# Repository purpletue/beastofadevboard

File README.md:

# BEEFCAKE 
*The absolute unit of a dual-MCU, hardwired, matrix-slinging, analog-crunching dev board.*

## What is BEEFCAKE?
BEEFCAKE isn't just a microcontroller board; it's a statement. Built out of sheer spite for unreliable wireless dropouts and a desire to completely over-engineer a hardware project, BEEFCAKE combines dual RP2040 microcontrollers, rock-solid hardwired Ethernet, an 8x8 LED matrix driven by a dedicated controller, an NFC reader/writer, and an ungodly number of GPIOs into a single top-mounted layout masterpiece.

## Key Features
* **Dual RP2040 Architecture:** 
  * **The Master ("Pimp"):** Handles heavy networking, system logic, and boasts 30 usable GPIOs.
  * **The Peripheral Slave ("Whore"):** Dedicated purely to analog-crunching, keeping its full suite of ADC channels completely pristine and isolated from digital noise.
* **Hardwired Ethernet:** Powered by a W5500 Ethernet stack and an RJ45 port because Wi-Fi is weak and cables are forever.
* **Matrix Vision:** Features an 8x8 LED matrix driven by a MAX7219 IC, paired with a custom NeoPixel button for maximum tactile satisfaction.
* **NFC Integration:** Built-in STMicroelectronics NFC reader/writer capabilities (ST25R3911B) for contactless sorcery.
* **Expansion Galore:** 
  * A 6-pin JST expansion connector wired straight to a clean SPI bus (3.3V, GND, SCK, MOSI, MISO, CS) to leave zero digital pins wasted.
  * A USB-C receptacle for power and programming.
* **Tactile Input:** On-board tactile buttons and test points for debugging sanity.

## Pinout & Hardware Specs
* **Total Master GPIO:** 30 available pins.
* **Total System ADCs:** 8 channels across the board (isolated cleanly on the slave).
* **Display Driver:** MAX7219 (SOIC-24 Wide) driving the 8x8 LED grid.
* **Network:** W5500 SPI Ethernet Controller + RJ45 with integrated magnetics.

---

### Serious now: AI Usage declaration.
This project uses AI in the README.md and nowhere else.

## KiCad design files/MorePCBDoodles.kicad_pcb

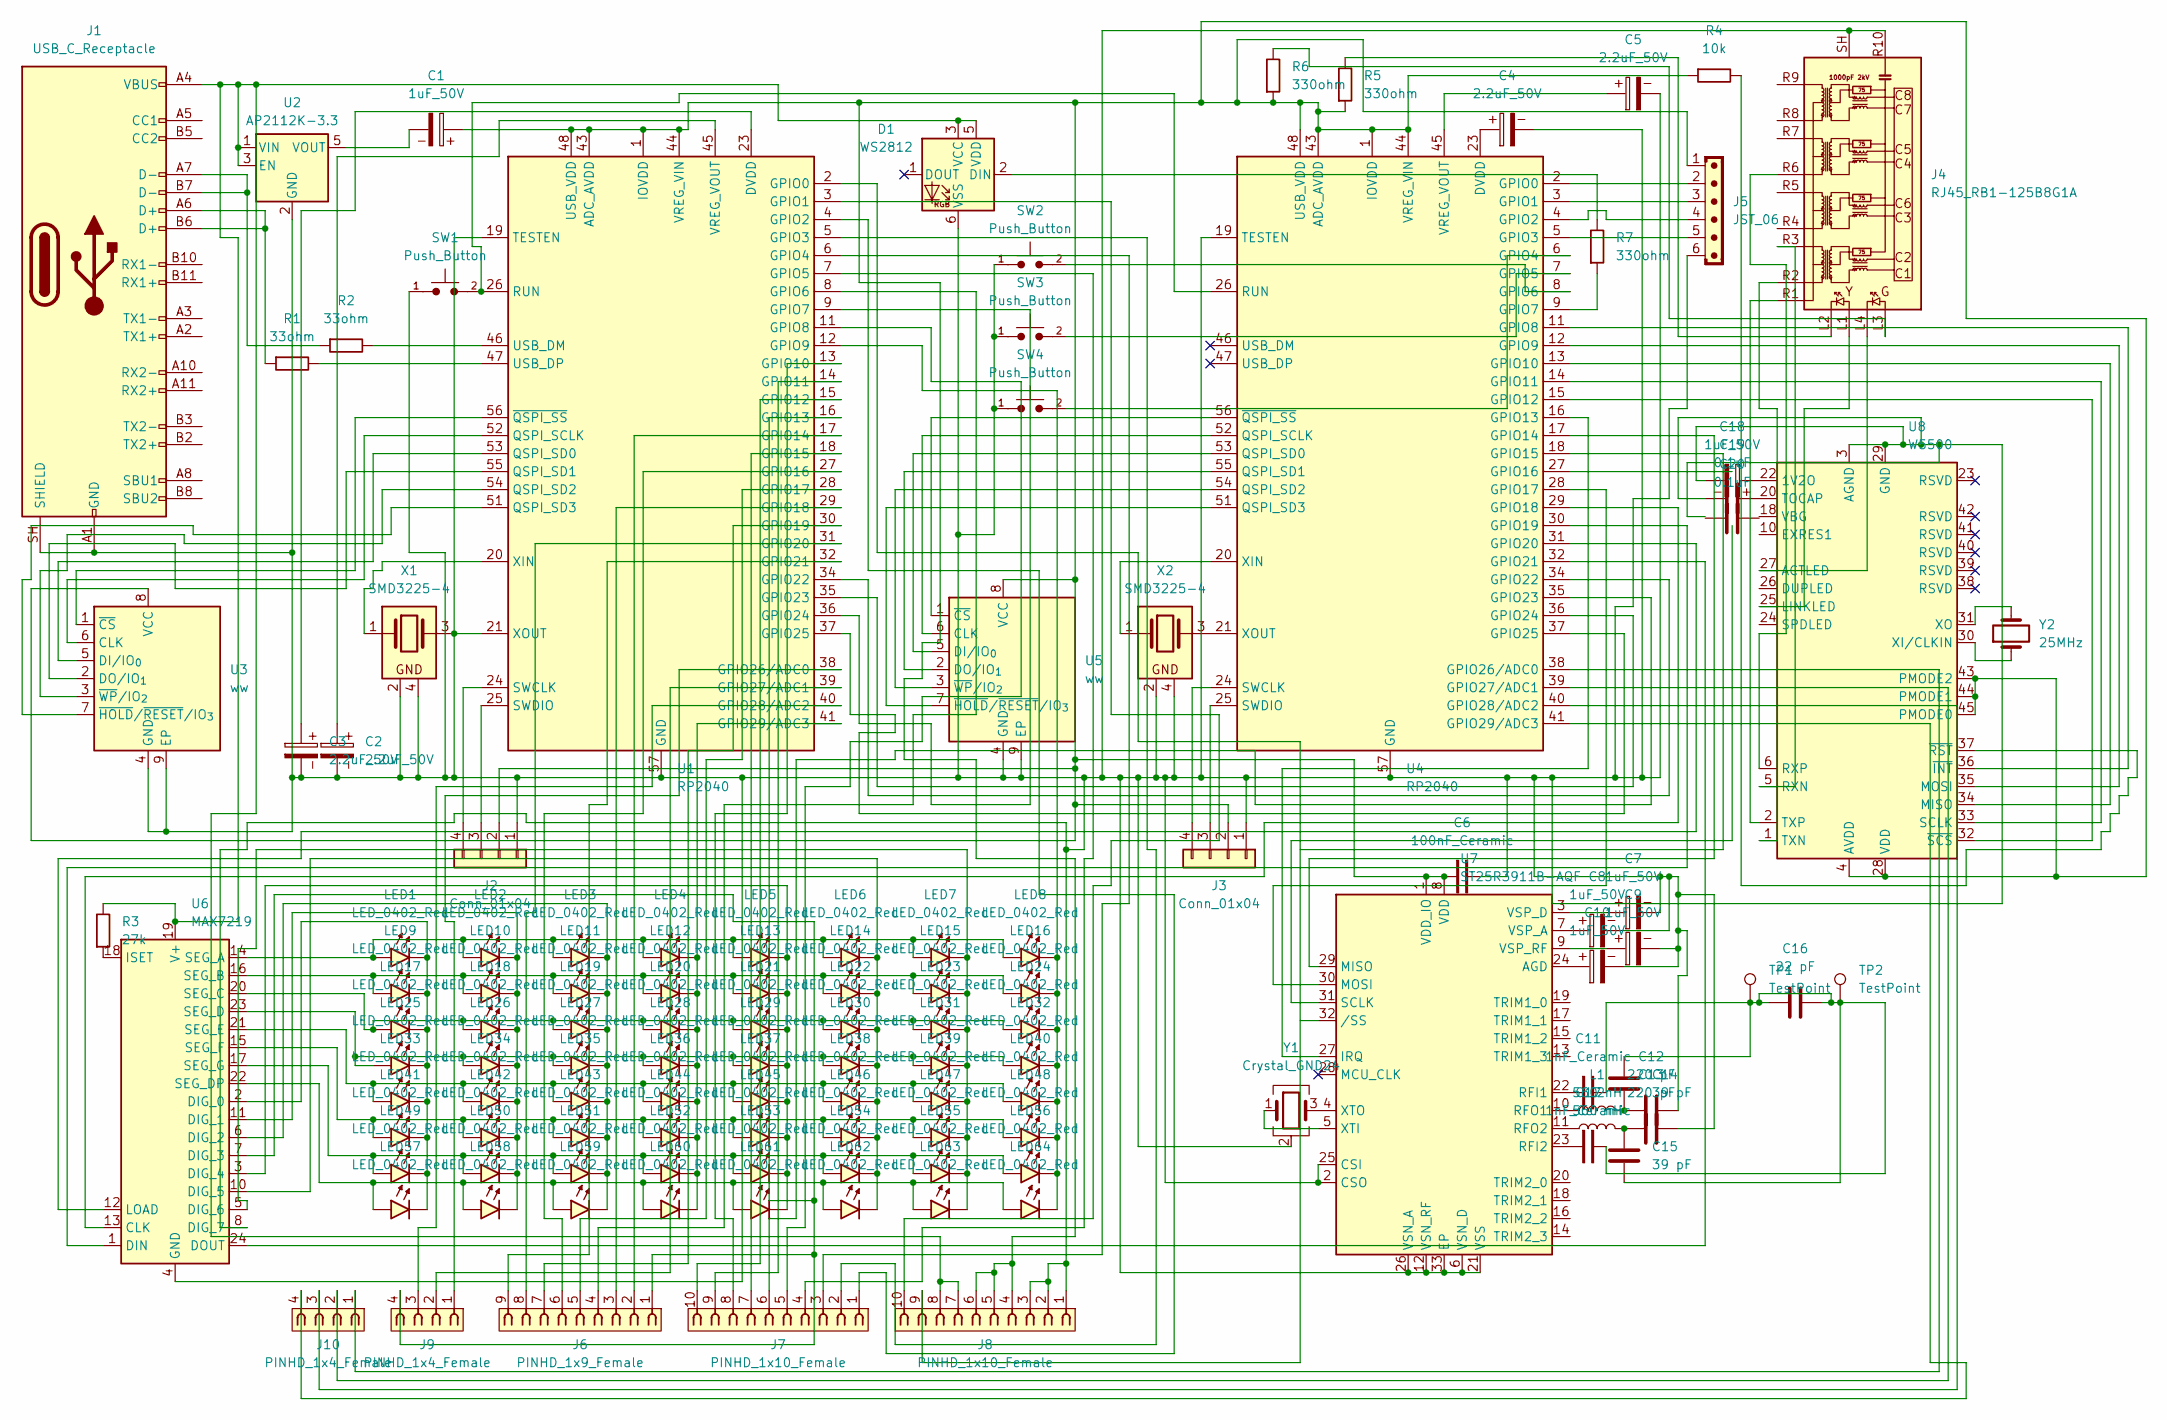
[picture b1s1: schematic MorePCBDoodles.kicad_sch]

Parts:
C1, C7, C8, C9, C10, C18: 1uF_50V; CP_Radial_D4.0mm_P1.50mm
C2, C3, C4, C5: 2.2uF_50V; CP_Radial_D4.0mm_P1.50mm
C6: 100nF_Ceramic; C_Disc_D5.0mm_W2.5mm_P2.50mm
C11, C17: 1nF_Ceramic; C_Disc_D5.0mm_W2.5mm_P2.50mm
C12, C13: 220 pF; CP_Axial_L10.0mm_D4.5mm_P15.00mm_Horizontal
C14, C15: 39 pF; CP_Axial_L10.0mm_D4.5mm_P15.00mm_Horizontal
C16: 22 pF; CP_Axial_L10.0mm_D4.5mm_P15.00mm_Horizontal
C19, C20: 0.1uF; CP_Elec_3x5.3
D1: WS2812; LED_WS2812_PLCC6_5.0x5.0mm_P1.6mm
J1: USB_C_Receptacle; USB_C_Receptacle_Amphenol_124019772112A
J2, J3: Conn_01x04; PinHeader_1x04_P1.00mm_Horizontal
J4: RJ45_RB1-125B8G1A; RJ45_UDE_RB1-125B8G1A
J5: JST_06; JST_EH_B6B-EH-A_1x06_P2.50mm_Vertical
J6: PINHD_1x9_Female; PinSocket_1x09_P2.54mm_Vertical
J7, J8: PINHD_1x10_Female; PinSocket_1x10_P2.54mm_Vertical
J9, J10: PINHD_1x4_Female; PinSocket_1x04_P2.54mm_Vertical
L1, L2: 560 nH; L_01005_0402Metric
LED1, LED2, LED3, LED4, LED5, LED6, LED7, LED8, LED9, LED10, LED11, LED12, LED13, LED14, LED15, LED16, LED17, LED18, LED19, LED20, LED21, LED22, LED23, LED24, LED25, LED26, LED27, LED28, LED29, LED30, LED31, LED32, LED33, LED34, LED35, LED36, LED37, LED38, LED39, LED40, LED41, LED42, LED43, LED44, LED45, LED46, LED47, LED48, LED49, LED50, LED51, LED52, LED53, LED54, LED55, LED56, LED57, LED58, LED59, LED60, LED61, LED62, LED63, LED64: LED_0402_Red; LED_0402_1005Metric
R1, R2: 33ohm; R_Axial_DIN0207_L6.3mm_D2.5mm_P10.16mm_Horizontal
R3: 27k; R_Axial_DIN0207_L6.3mm_D2.5mm_P10.16mm_Horizontal
R4: 10k; R_Axial_DIN0207_L6.3mm_D2.5mm_P10.16mm_Horizontal
R5, R6, R7: 330ohm; R_Axial_DIN0207_L6.3mm_D2.5mm_P10.16mm_Horizontal
SW1, SW2, SW3, SW4: Push_Button; SW_SPST_TS-1088-xR020
TP1, TP2: TestPoint; TestPoint_Pad_1.0x1.0mm
U1, U4: RP2040; QFN-56-1EP_7x7mm_P0.4mm_EP3.2x3.2mm
U2: AP2112K-3.3; SOT-23-5
U3, U5: ww; WSON-8-1EP_8x6mm_P1.27mm_EP3.4x4.3mm
U6: MAX7219; SOIC-24W_7.5x15.4mm_P1.27mm
U7: ST25R3911B-AQF; QFN-32-1EP_5x5mm_P0.5mm_EP3.6x3.6mm_ThermalVias
U8: W5500; LQFP-48_7x7mm_P0.5mm
X1, X2: SMD3225-4; Crystal_SMD_3225-4Pin_3.2x2.5mm
Y1: Crystal_GND24; Crystal_SMD_3225-4Pin_3.2x2.5mm
Y2: 25MHz; Crystal_SMD_3225-4Pin_3.2x2.5mm

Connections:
unnamed: C3.1, U1.23 (DVDD), U1.50 (DVDD)
unnamed: C4.1, U4.23 (DVDD), U4.50 (DVDD)
unnamed: C11.2, C14.2, C15.1, C16.1, C16.2, C17.2, TP1.1 (1_1), TP2.1 (1_1)
unnamed: C12.1, C14.1, L1.2
unnamed: C13.1, C15.2, L2.2
unnamed: D1.2 (DIN), R7.2
unnamed: D1.3 (VCC), D1.5 (VDD), J1.A4 (VBUS), J1.A9 (VBUS), J1.B4 (VBUS), J1.B9 (VBUS), J8.7, J8.8, R3.2, U2.1 (VIN), U2.3 (EN), U6.19 (V+)
unnamed: C2.2, C3.2, C4.2, C5.2, C6.2, C7.2, C8.2, C9.2, C10.2, C12.2, C13.2, C18.2, C19.2, D1.6 (VSS), J1.A1 (GND), J1.A12 (GND), J1.B1 (GND), J1.B12 (GND), J1.SH (SHIELD), J2.1, J3.1, J4.R10 (GND), J4.SH, J5.6, J8.1, J8.2, J8.3, SW1.1, SW2.1, SW3.1, SW4.1, U1.19 (TESTEN), U1.21 (XOUT), U1.57 (GND), U2.2 (GND), U3.4 (GND), U3.9 (EP), U4.19 (TESTEN), U4.57 (GND), U5.4 (GND), U5.9 (EP), U6.4 (GND), U6.8 (DIG_7), U6.9 (GND), U7.2 (CSO), U7.6 (VSN_D), U7.12 (VSN_RF), U7.21 (VSS), U7.25 (CSI), U7.26 (VSN_A), U7.33 (EP), U8.3 (AGND), U8.9 (AGND), U8.14 (AGND), U8.16 (AGND), U8.19 (AGND), U8.29 (GND), U8.48 (AGND), X1.2, X1.3, X1.4, X2.2, X2.4, Y1.2 (G), Y1.4 (G)
unnamed: J1.A6 (D+), J1.B6 (D+), R1.1
unnamed: J1.A7 (D-), J1.B7 (D-), R2.1
unnamed: C1.1, C6.1, J2.2, J3.2, J5.1, J8.4, J8.5, J8.6, R4.1, R5.1, R6.1, U1.1 (IOVDD), U1.10 (IOVDD), U1.22 (IOVDD), U1.33 (IOVDD), U1.42 (IOVDD), U1.43 (ADC_AVDD), U1.44 (VREG_VIN), U1.48 (USB_VDD), U1.49 (IOVDD), U3.8 (VCC), U4.1 (IOVDD), U4.10 (IOVDD), U4.22 (IOVDD), U4.33 (IOVDD), U4.42 (IOVDD), U4.43 (ADC_AVDD), U4.44 (VREG_VIN), U4.48 (USB_VDD), U4.49 (IOVDD), U5.8 (VCC), U7.1 (VDD_IO), U7.8 (VDD), U8.4 (AVDD), U8.8 (AVDD), U8.11 (AVDD), U8.15 (AVDD), U8.17 (AVDD), U8.21 (AVDD), U8.28 (VDD), U8.43 (PMODE2), U8.44 (PMODE1), U8.45 (PMODE0)
unnamed: J2.3, U1.25 (SWDIO)
unnamed: J2.4, U1.24 (SWCLK)
unnamed: J3.3, U4.25 (SWDIO)
unnamed: J3.4, U4.24 (SWCLK)
unnamed: J4.R1 (CT), U8.2 (TXP)
unnamed: J4.L2, R5.2
unnamed: J4.L3, R6.2
unnamed: J4.R2 (TD1+), U8.1 (TXN)
unnamed: J4.R3 (TD1-), U8.5 (RXN)
unnamed: J4.R6 (TD3+), U8.6 (RXP)
unnamed: LED1.2 (A), LED2.2 (A), LED3.2 (A), LED4.2 (A), LED5.2 (A), LED6.2 (A), LED7.2 (A), LED8.2 (A), U6.14 (SEG_A)
unnamed: LED1.1 (K), LED9.1 (K), LED17.1 (K), LED25.1 (K), LED33.1 (K), LED41.1 (K), LED49.1 (K), LED57.1 (K), U6.2 (DIG_0)
unnamed: LED9.2 (A), LED10.2 (A), LED11.2 (A), LED12.2 (A), LED13.2 (A), LED14.2 (A), LED15.2 (A), LED16.2 (A), U6.16 (SEG_B)
unnamed: LED2.1 (K), LED10.1 (K), LED18.1 (K), LED26.1 (K), LED34.1 (K), LED42.1 (K), LED50.1 (K), LED58.1 (K), U6.11 (DIG_1)
unnamed: LED3.1 (K), LED11.1 (K), LED19.1 (K), LED27.1 (K), LED35.1 (K), LED43.1 (K), LED51.1 (K), LED59.1 (K), U6.6 (DIG_2)
unnamed: LED4.1 (K), LED12.1 (K), LED20.1 (K), LED28.1 (K), LED36.1 (K), LED44.1 (K), LED52.1 (K), LED60.1 (K), U1.41 (GPIO29/ADC3)
unnamed: LED5.1 (K), LED13.1 (K), LED21.1 (K), LED29.1 (K), LED37.1 (K), LED45.1 (K), LED53.1 (K), LED61.1 (K), U6.3 (DIG_4)
unnamed: LED6.1 (K), LED14.1 (K), LED22.1 (K), LED30.1 (K), LED38.1 (K), LED46.1 (K), LED54.1 (K), LED62.1 (K), U6.10 (DIG_5)
unnamed: LED7.1 (K), LED15.1 (K), LED23.1 (K), LED31.1 (K), LED39.1 (K), LED47.1 (K), LED55.1 (K), LED63.1 (K), U6.5 (DIG_6)
unnamed: LED8.1 (K), LED16.1 (K), LED24.1 (K), LED32.1 (K), LED40.1 (K), LED48.1 (K), LED56.1 (K), LED64.1 (K), U1.12 (GPIO9)
unnamed: LED17.2 (A), LED18.2 (A), LED19.2 (A), LED20.2 (A), LED21.2 (A), LED22.2 (A), LED23.2 (A), LED24.2 (A), U6.20 (SEG_C)
unnamed: LED25.2 (A), LED26.2 (A), LED27.2 (A), LED28.2 (A), LED29.2 (A), LED30.2 (A), LED31.2 (A), LED32.2 (A), U6.23 (SEG_D)
unnamed: LED33.2 (A), LED34.2 (A), LED35.2 (A), LED36.2 (A), LED37.2 (A), LED38.2 (A), LED39.2 (A), LED40.2 (A), U6.21 (SEG_E)
unnamed: LED41.2 (A), LED42.2 (A), LED43.2 (A), LED44.2 (A), LED45.2 (A), LED46.2 (A), LED47.2 (A), LED48.2 (A), U6.15 (SEG_F)
unnamed: LED49.2 (A), LED50.2 (A), LED51.2 (A), LED52.2 (A), LED53.2 (A), LED54.2 (A), LED55.2 (A), LED56.2 (A), U6.17 (SEG_G)
unnamed: LED57.2 (A), LED58.2 (A), LED59.2 (A), LED60.2 (A), LED61.2 (A), LED62.2 (A), LED63.2 (A), LED64.2 (A), U6.22 (SEG_DP)
unnamed: J8.9, U1.2 (GPIO0)
unnamed: J8.10, U1.3 (GPIO1)
unnamed: J7.1, U1.4 (GPIO2)
unnamed: J7.2, U1.5 (GPIO3)
unnamed: J7.3, U1.6 (GPIO4)
unnamed: J7.4, U1.7 (GPIO5)
unnamed: J6.4, U1.8 (GPIO6)
unnamed: J7.5, U1.11 (GPIO8)
unnamed: J7.8, U1.13 (GPIO10)
unnamed: J7.9, U1.14 (GPIO11)
unnamed: J7.10, U1.15 (GPIO12)
unnamed: J6.1, J9.4, U1.16 (GPIO13), U6.7 (DIG_3)
unnamed: J6.2, U1.17 (GPIO14)
unnamed: J7.7, U1.18 (GPIO15)
unnamed: J6.6, U1.27 (GPIO16)
unnamed: J6.5, U1.28 (GPIO17)
unnamed: J6.3, U1.29 (GPIO18)
unnamed: J6.7, U1.30 (GPIO19)
unnamed: J6.8, U1.31 (GPIO20)
unnamed: J6.9, U1.32 (GPIO21)
unnamed: U1.34 (GPIO22), U4.34 (GPIO22)
unnamed: U1.35 (GPIO23), U4.36 (GPIO24)
unnamed: U1.9 (GPIO7), U1.36 (GPIO24)
unnamed: U1.37 (GPIO25), U4.37 (GPIO25)
unnamed: J9.1, U1.38 (GPIO26/ADC0)
unnamed: J9.2, U1.39 (GPIO27/ADC1)
unnamed: J9.3, U1.40 (GPIO28/ADC2)
unnamed: U1.52 (QSPI_SCLK), U3.6 (CLK)
unnamed: U1.53 (QSPI_SD0), U3.5 (DI/IO_{0})
unnamed: U1.55 (QSPI_SD1), U3.2 (DO/IO_{1})
unnamed: U1.54 (QSPI_SD2), U3.3 (~WP/IO_{2})
unnamed: U1.51 (QSPI_SD3), U3.7 (~HOLD/~RESET/IO_{3})
unnamed: SW1.2, U1.26 (RUN), U4.26 (RUN)
unnamed: R2.2, U1.46 (USB_DM)
unnamed: R1.2, U1.47 (USB_DP)
unnamed: C2.1, U1.45 (VREG_VOUT)
unnamed: U1.20 (XIN), X1.1
unnamed: U1.56 (~QSPI_SS), U3.1 (~CS)
unnamed: C1.2, U2.5 (VOUT)
unnamed: J5.2, U4.2 (GPIO0)
unnamed: J5.3, U4.3 (GPIO1)
unnamed: J5.4, U4.4 (GPIO2)
unnamed: J5.5, U4.5 (GPIO3)
unnamed: SW4.2, U4.6 (GPIO4)
unnamed: SW3.2, U4.7 (GPIO5)
unnamed: SW2.2, U4.8 (GPIO6)
unnamed: R7.1, U4.9 (GPIO7)
unnamed: U4.11 (GPIO8), U8.36 (~INT)
unnamed: U4.12 (GPIO9), U8.35 (MOSI)
unnamed: U4.13 (GPIO10), U8.34 (MISO)
unnamed: U4.14 (GPIO11), U8.33 (SCLK)
unnamed: U4.15 (GPIO12), U8.32 (~SCS)
unnamed: U4.16 (GPIO13), U7.27 (IRQ)
unnamed: U4.17 (GPIO14), U7.29 (MISO)
unnamed: U4.28 (GPIO17), U7.30 (MOSI)
unnamed: U4.29 (GPIO18), U6.13 (CLK)
unnamed: U4.30 (GPIO19), U6.1 (DIN)
unnamed: U4.31 (GPIO20), U6.12 (LOAD)
unnamed: U4.32 (GPIO21), U6.24 (DOUT)
unnamed: J7.6, U4.35 (GPIO23)
unnamed: J10.1, U4.38 (GPIO26/ADC0)
unnamed: J10.2, U4.39 (GPIO27/ADC1)
unnamed: J10.3, U4.40 (GPIO28/ADC2)
unnamed: J10.4, U4.41 (GPIO29/ADC3)
unnamed: U4.52 (QSPI_SCLK), U5.6 (CLK)
unnamed: U4.53 (QSPI_SD0), U5.5 (DI/IO_{0})
unnamed: U4.55 (QSPI_SD1), U5.2 (DO/IO_{1})
unnamed: U4.54 (QSPI_SD2), U5.3 (~WP/IO_{2})
unnamed: U4.51 (QSPI_SD3), U5.7 (~HOLD/~RESET/IO_{3})
unnamed: C5.1, U4.45 (VREG_VOUT)
unnamed: U4.20 (XIN), X2.1
unnamed: U4.21 (XOUT), X2.3
unnamed: U4.56 (~QSPI_SS), U5.1 (~CS)
unnamed: R3.1, U6.18 (ISET)
unnamed: C10.1, U7.24 (AGD)
unnamed: C11.1, U7.22 (RFI1)
unnamed: C17.1, U7.23 (RFI2)
unnamed: L1.1, U7.10 (RFO1)
unnamed: L2.1, U7.11 (RFO2)
unnamed: C8.1, U7.7 (VSP_A)
unnamed: C7.1, U7.3 (VSP_D)
unnamed: C9.1, U7.9 (VSP_RF)
unnamed: U7.5 (XTI), Y1.1
unnamed: U7.4 (XTO), Y1.3
unnamed: C18.1, U8.22 (1V2O)
unnamed: J4.L4, U8.27 (ACTLED)
unnamed: J4.L1, U8.25 (LINKLED)
unnamed: C19.1, U8.20 (TOCAP)
unnamed: U8.30 (XI/CLKIN), Y2.1
unnamed: U8.31 (XO), Y2.2
unnamed: R4.2, U8.37 (~RST)

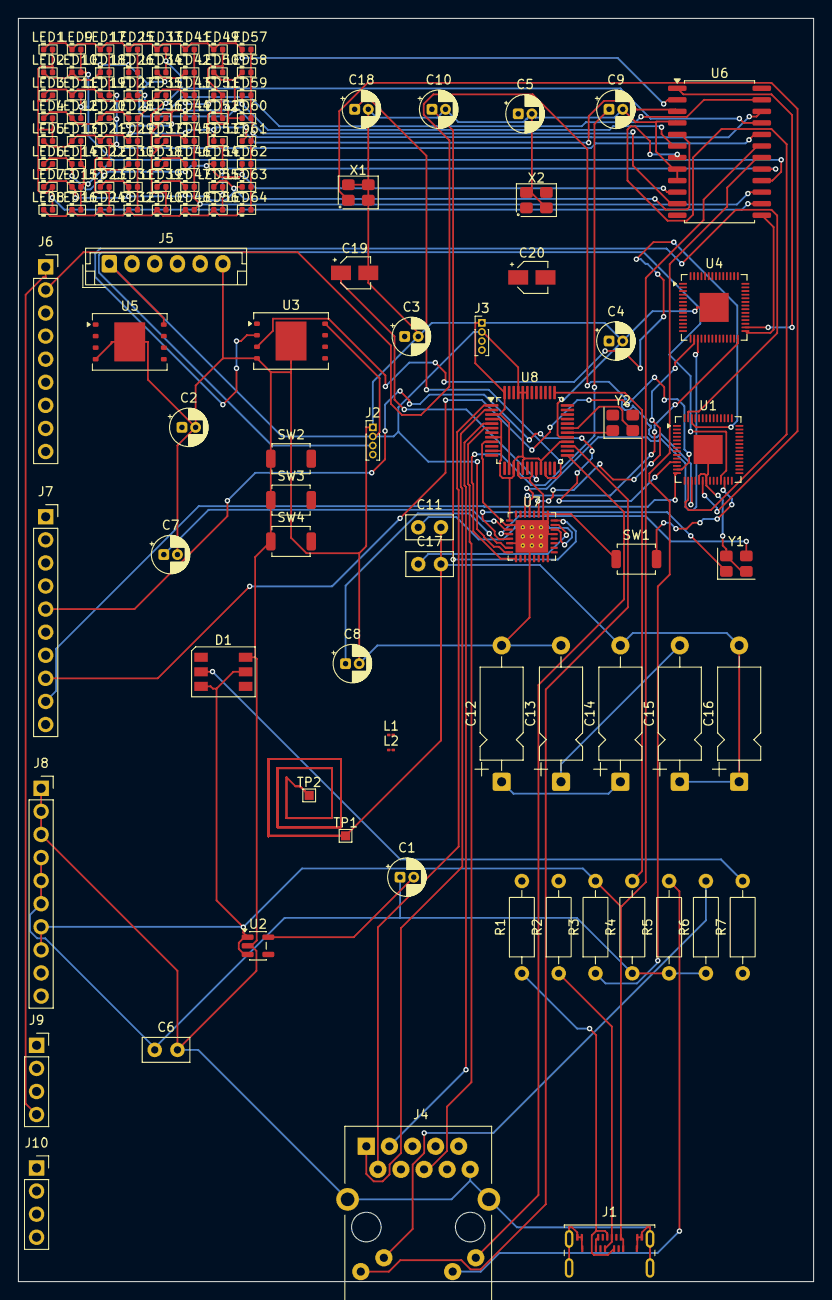
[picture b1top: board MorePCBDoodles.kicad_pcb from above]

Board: 2 copper layers, 87.5 x 139.0 mm, 122 parts (0 on the bottom side), 128 nets.

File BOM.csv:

"Id";"Designator";"Footprint";"Quantity";"Designation";"Supplier and ref";
1;"C1, C7, C8, C9, C10, C18";"CP_Radial_D4.0mm_P1.50mm";6;"1uF_50V";;;
2;"C2, C3, C4, C5";"CP_Radial_D4.0mm_P1.50mm";4;"2.2uF_50V";;;
3;"C6";"C_Disc_D5.0mm_W2.5mm_P2.50mm";1;"100nF_Ceramic";;;
4;"C11, C17";"C_Disc_D5.0mm_W2.5mm_P2.50mm";2;"1nF_Ceramic";;;
5;"C12, C13";"CP_Axial_L10.0mm_D4.5mm_P15.00mm_Horizontal";2;"220 pF";;;
6;"C14, C15";"CP_Axial_L10.0mm_D4.5mm_P15.00mm_Horizontal";2;"39 pF";;;
7;"C16";"CP_Axial_L10.0mm_D4.5mm_P15.00mm_Horizontal";1;"22 pF";;;
8;"C19, C20";"CP_Elec_3x5.3";2;"0.1uF";;;
9;"D1";"LED_WS2812_PLCC6_5.0x5.0mm_P1.6mm";1;"WS2812";;;
10;"J1";"USB_C_Receptacle_Amphenol_124019772112A";1;"USB_C_Receptacle";;;
11;"J2, J3";"PinHeader_1x04_P1.00mm_Vertical";2;"Conn_01x04";;;
12;"J4";"RJ45_UDE_RB1-125B8G1A";1;"RJ45_RB1-125B8G1A";;;
13;"J5";"JST_EH_B6B-EH-A_1x06_P2.50mm_Vertical";1;"JST_06";;;
14;"L1, L2";"L_01005_0402Metric";2;"560 nH";;;
15;"LED1, LED2, LED3, LED4, LED5, LED6, LED7, LED8, LED9, LED10, LED11, LED12, LED13, LED14, LED15, LED16, LED17, LED18, LED19, LED20, LED21, LED22, LED23, LED24, LED25, LED26, LED27, LED28, LED29, LED30, LED31, LED32, LED33, LED34, LED35, LED36, LED37, LED38, LED39, LED40, LED41, LED42, LED43, LED44, LED45, LED46, LED47, LED48, LED49, LED50, LED51, LED52, LED53, LED54, LED55, LED56, LED57, LED58, LED59, LED60, LED61, LED62, LED63, LED64";"LED_0402_1005Metric";64;"LED_0402_Red";;;
16;"R1, R2";"R_Axial_DIN0207_L6.3mm_D2.5mm_P10.16mm_Horizontal";2;"33ohm";;;
17;"R3";"R_Axial_DIN0207_L6.3mm_D2.5mm_P10.16mm_Horizontal";1;"27k";;;
18;"R4";"R_Axial_DIN0207_L6.3mm_D2.5mm_P10.16mm_Horizontal";1;"10k";;;
19;"R5, R6, R7";"R_Axial_DIN0207_L6.3mm_D2.5mm_P10.16mm_Horizontal";3;"330ohm";;;
20;"SW1, SW2, SW3, SW4";"SW_SPST_TS-1088-xR020";4;"Push_Button";;;
21;"U1, U4";"QFN-56-1EP_7x7mm_P0.4mm_EP3.2x3.2mm";2;"RP2040";;;
22;"U2";"SOT-23-5";1;"AP2112K-3.3";;;
23;"U3, U5";"WSON-8-1EP_8x6mm_P1.27mm_EP3.4x4.3mm";2;"ww";;;
24;"U6";"SOIC-24W_7.5x15.4mm_P1.27mm";1;"MAX7219";;;
25;"U7";"QFN-32-1EP_5x5mm_P0.5mm_EP3.6x3.6mm_ThermalVias";1;"ST25R3911B-AQF";;;
26;"U8";"LQFP-48_7x7mm_P0.5mm";1;"W5500";;;
27;"X1, X2";"Crystal_SMD_3225-4Pin_3.2x2.5mm";2;"SMD3225-4";;;
28;"Y1";"Crystal_SMD_3225-4Pin_3.2x2.5mm";1;"Crystal_GND24";;;
29;"Y2";"Crystal_SMD_3225-4Pin_3.2x2.5mm";1;"25MHz";;;
